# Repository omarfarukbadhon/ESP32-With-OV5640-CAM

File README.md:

## ESP32 With OV5640 CAM 

# 3D of top side PCB 

# 3D of Bottom Side PCB

# Routing of PCB

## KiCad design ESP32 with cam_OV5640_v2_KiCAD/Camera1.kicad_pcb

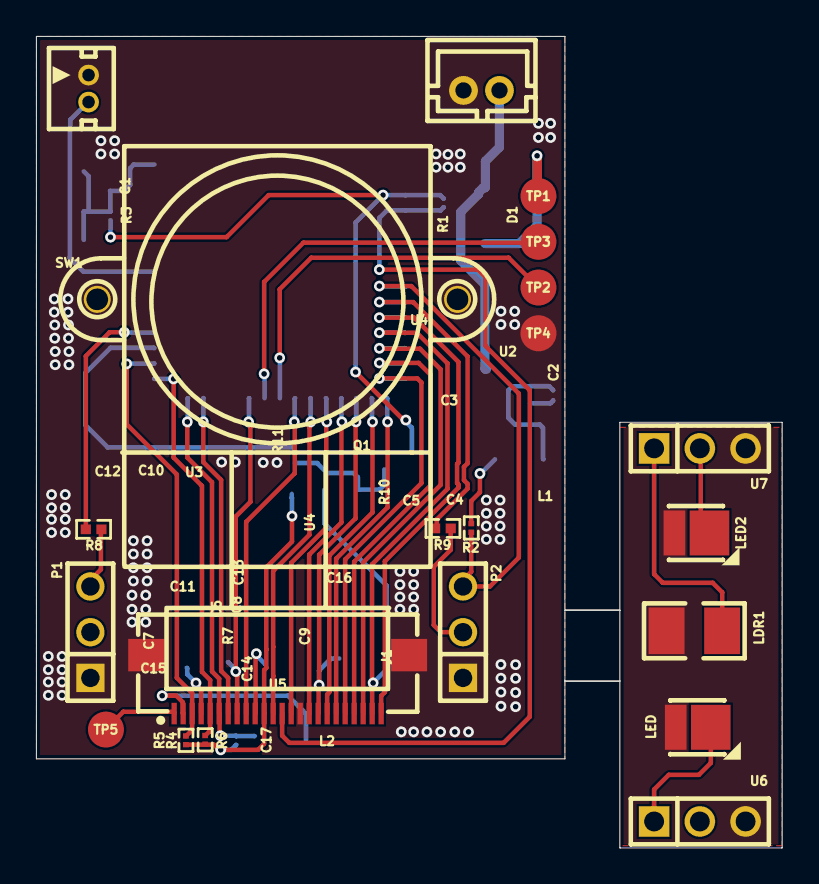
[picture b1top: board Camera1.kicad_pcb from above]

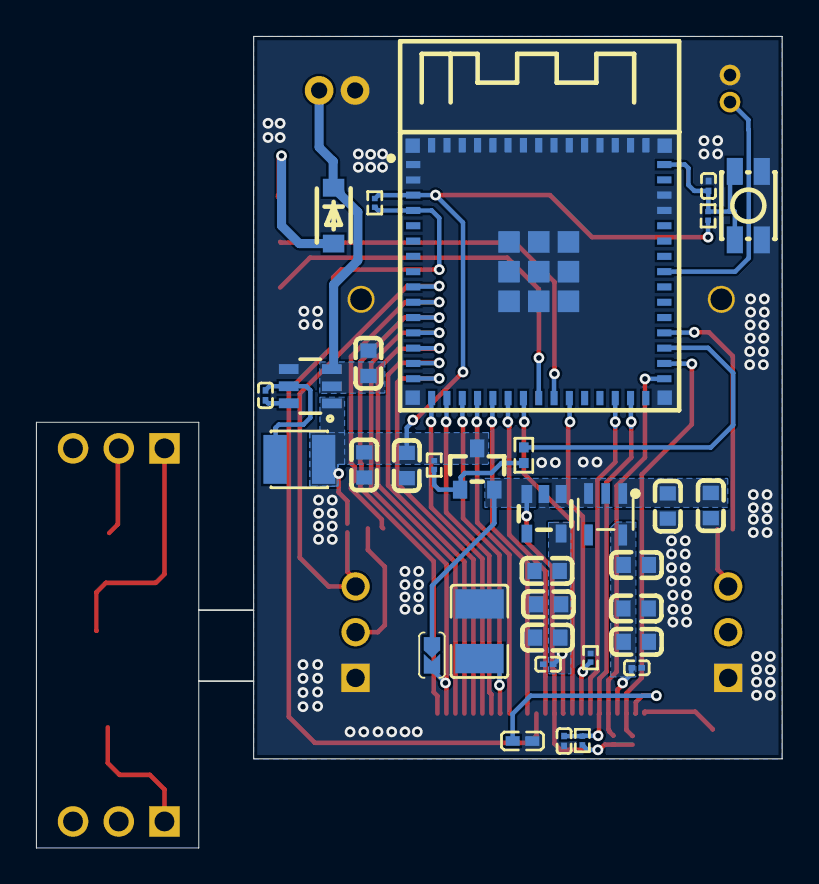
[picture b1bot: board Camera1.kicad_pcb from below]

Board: 2 copper layers, 41.4 x 45.1 mm, 54 parts (33 on the bottom side), 44 nets.

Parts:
C1, C2, C14, C15, C17: 100NF SMD CERAMIC 201
C3, C6, C7, C8, C9: 10UF SMD CERAMIC 603
C4, C5: 22PF SMD CERAMIC 603
C10, C11, C12, C13: 1UF CAP
C16: 22UF SMD CERAMIC 1210
CN1: CONNECTOR 2P
CN2: 2P WHITE CONNECTOR 1.5MM
D1: SCHOTTKY DIODE
J1: PAD-JUMPER-2
L1: 3.9UH POWER INDUCTOR
L2: FERRITE
LDR1: LDR
LED, LED2: LED SMD
P1, P2: 3P FH 2.54MM
Q1: P CHANNEL MSFET (AO3401A1)
R1, R3, R4, R5, R6, R7, R10: 10K SMD CERAMIC 201
R2: 4K7 SMD 201
R8, R9, R11: 100R 402
SW1: PUSH BUTTON 4P
TP1, TP2, TP3, TP4, TP5: TESTPOINT
U1: ESP32-S3-MINI-1-N8
U2: 3V3 CONVERTER (AP63203)
U3: 2V8 CONVERTER (TLV74328)
U4: OV5640
U4#2: 1V5 CONVERTER (TLV74215)
U5: CAMERA CONNECTOR
U6, U7: 3P MH 2.54MM

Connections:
+1V5: C8.2, C9.2, C13.2, C14.2, U4#2.5, U5.10
+2V8: C6.2, C7.2, C11.2, C15.2, U3.5, U5.4
+3V3: C4.2, C5.2, L1.2, Q1.3, R1.2, R2.1, R3.2, R10.1, U1.3, U2.1
+3V3_CAM: C10.2, C12.2, J1.1, Q1.2, R4.2, R5.2, R6.2, U3.1, U3.3, U4#2.1, U4#2.3, U5.11
AGND: L2.2, U5.2
BAT: C3.2, CN1.1, D1.1, U2.2, U2.3
CAM_PWR: R11.1, U1.33
DATA0: U1.11, U5.24
DATA1: J1.2, U1.12, U5.23
DATA2: U1.16, U5.19
DATA3: U1.14, U5.21
DATA4: U1.13, U5.22
DATA5: U1.15, U5.20
DATA6: U1.17, U5.18
DATA7: U1.19, U5.16
DATA8: U1.20, U5.14
DATA9: U1.21, U5.12
GND: C1.1, C3.1, C4.1, C5.1, C6.1, C7.1, C8.1, C9.1, C10.1, C11.1, C12.1, C13.1, C14.1, C15.1, C16.1, C17.1, CN1.2, CN2.1, L2.1, P1.1, P2.1, R7.1, SW1.3, SW1.4, TP4.1, U1.1, U1.2, U1.42, U1.43, U1.46, U1.47, U1.48, U1.49, U1.50, U1.51, U1.52, U1.53, U1.54, U1.55, U1.56, U1.57, U1.58, U1.59, U1.60, U1.GND, U2.4, U3.2, U4#2.2, U5.15, U5.25, U5.26
HSYNC: U1.22, U5.9
IR_CUT: CN2.2, U1.38
LDR: LDR1.2, U7.1
LDR_MCU: P2.3, R2.2, U1.9
LED1: R8.2, U1.34
LED2: R9.2, U1.10
NetC2_1: C2.1, L1.1, U2.5
NetC2_2: C2.2, U2.6
NetQ1_1: Q1.1, R10.2, R11.2
NetTP5_1: TP5.1, U5.1
PCLK: C16.2, U1.18, U5.17
PWDN: R7.2, U1.25, U5.8
RESET: C17.2, R6.1, U1.29, U5.6
RST: C1.2, R3.1, SW1.1, SW1.2, U1.45
SCL: R4.1, U1.31, U5.5
SDA: R5.1, U1.32, U5.3
USB_N: TP2.1, U1.23
USB_P: TP3.1, U1.24
Up1: P1.3, R8.1
Up2: P2.2, R9.1
Up11: LED.2, U6.1
Up22: LED2.2, U7.2
Up_GND: LDR1.1, LED.1, LED2.1, U6.3, U7.3
VSYNC: U1.28, U5.7
XCLK: R1.1, U1.4, U5.13
usb_5V: D1.2, TP1.1

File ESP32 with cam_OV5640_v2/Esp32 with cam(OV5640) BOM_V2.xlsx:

Comment | Description | Designator | Footprint | LibRef | Quantity | Input Voltage | Manufacturer | Manufacturer Part | Maximum Input Voltage | Output Voltage | Supplier Part | Tolerance
TEST POINT |  | +5V, D-, D+, GND, STROBE | TESTPOINT | TEST POINT | 5
100nF | 10V 100nF X5R ±10% 0201 Multilayer Ceramic Capacitors MLCC - SMD/SMT ROHS | C1, C2, C14, C15, C17 | 100nF SMD Ceramic 201 | 100nF SMD Ceramic 201 | 5 |  | muRata(村田) | GRM033R61A104KE84D |  |  | C161466 | ±10%
10uF | 10V 10uF B ±10% 0603 Multilayer Ceramic Capacitors MLCC - SMD/SMT ROHS | C3, C6, C7, C8, C9 | 10uF SMD Ceramic 603 | 10uF SMD Ceramic 603 | 5 |  | muRata(村田) | GRM188B31A106KE69D |  |  | C469532
22pF | 16V 22pF C0G ±5% 0603 Multilayer Ceramic Capacitors MLCC - SMD/SMT ROHS | C4, C5 | 22pF SMD Ceramic 603 | 22pF SMD Ceramic 603 | 2 |  | KEMET(基美) | C0603C220J4GAC7867 |  |  | C561800 | ±5%
1uF | 16V 1uF Y5V -20%~+80% 0603 Multilayer Ceramic Capacitors MLCC - SMD/SMT ROHS | C10, C11, C12, C13 | 1uF Cap | 1uF Ceramic SMD 603 | 4 |  | SAMWHA(三和) | CS1608Y5V105Z160NRB |  |  | C5189821 | -20%~+80%
22uF | 10V 22uF X7R ±10% 1210 Multilayer Ceramic Capacitors MLCC - SMD/SMT ROHS | C16 | 22uF SMD Ceramic 1210 | 22uF SMD Ceramic 1210 | 1 |  | KEMET(基美) | C1210C226K8RACAUTO |  |  | C561843 | ±10%
B2B-PH-K-S(LF)(SN) | 1x2P 2P PH Tin 2 -25℃~+85℃ 2A 1 2mm Brass Direct Insert Plugin,P=2mm Wire To Bo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 | CN1 | Connector 2P | Connector 2P | 1 |  | JST | B2B-PH-K-S(LF)(SN) |  |  | C131337
HDGC1501WV-2P |  | CN2 | 2P white Connector 1.5mm | 2P Connector 1.5mm | 1 |  | HDGC(华德共创) | HDGC1501WV-2P |  |  | C5175212
MBR120VLSFT1G | 20V 300mV@1A 1A SOD-123FL Schottky Diodes ROHS | D1 | Schottky Diode | Schottky Diode | 1 |  | onsemi(安森美) | MBR120VLSFT1G |  |  | C223608
Jumper | SMD JUMPER | J1 | PAD-JUMPER-2 | JUMPER SOLDER BRIDGE | 1
3.9uH | 1.5A 3.9uH ±20% 1.4A SMD,3x3mm Power Inductors ROHS | L1 | 3.9uH power Inductor | 3.9uH SMD PI | 1 |  | cjiang(长江微电) | FNR3015S3R9MT |  |  | C167751 | ±20%
BLM15AG601SN1D | 520mΩ ±25% 600Ω@100MHz 0402 Ferrite Beads ROHS | L2 | Ferrite | BLM15AG601SN1D | 1 |  | muRata(村田) | BLM15AG601SN1D |  |  | C76884 | ±25%
GT36528 | SMD,2.4x3.6mm Photoresistors ROHS | LDR1 | LDR | LDR | 1 |  | JCHL(晶创和立) | GT36528 |  |  | C2904881
XYC-IRC18C-24 |  | LED1, LED2 | LED SMD | LED SMD | 2 |  | NEWOPTO(鑫永诚光电) | XYC-IRC18C-24 |  |  | C2988733
Header-Female-2.54_1x3 |  | P1, P2 | 3P FH 2.54mm | Header-Female-2.54_1x3 | 2 |  | BOOMELE(博穆精密) | 2.54-1*3P母 |  |  | C146243
P_Mos | 30V 4A 44mΩ@10V,4.3A 1.4W 1.3V@250uA 1 Piece P-Channel SOT-23 MOSFETs ROHS | Q1 | P channel msfet (AO3401A1) | P channel msfet (AO3401A1) | 1 |  | AOS | AO3401A |  |  | C15127
10K | 50mW Thick Film Resistors 25V ±1% ±200ppm/℃ 10kΩ 0201 Chip Resistor - Surface M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 | R1, R3, R4, R5, R6, R7, R10 | 10K SMD Ceramic 201 | 10K SMD Ceramic 201 | 7 |  | YAGEO(国巨) | AF0201FR-0710KL |  |  | C143978 | ±1%
100R | 100mW Thick Film Resistors ±100ppm/℃ ±1% 100Ω 0402 Chip Resistor - Surface Moun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 | R8, R9, R11 | 100R 402 | 100R 402 | 3 |  | PANASONIC(松下) | ERJ2RKF1000X |  |  | C413063 | ±1%
TS-1102-5516 | 6mm 5.5mm Round Button 25mA Direct Insert 6mm SPST 100000 Times 1.6N 24V Plugin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 | RST | Push Button 4P | Push Button 4P | 1 |  | SOFNG(硕方) | TS-1102-5516 |  |  | C183624
ESP32-S3-MINI-1-N4R2 |  | U1 | ESP32-S3-MINI-1-N8 | ESP32-S3-MINI-1-N4R2 | 1 |  | ESPRESSIF(乐鑫) | ESP32-S3-MINI-1-N4R2 |  |  | C3013941
AP63203WU-7 | Step-down type Fixed 2A 3.3V 3.8V~32V TSOT-23-6 DC-DC Converters ROHS | U2 | 3V3 Converter (AP63203) | AP63203 | 1 | 3.8V~32V | DIODES(美台) | AP63203WU-7 |  | 3.3V | C780769
TLV74328PDBVR | 300mA 68dB Fixed 2.8V Positive electrode 5.5V SOT-23-5 Voltage Regulators - Lin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 | U3 | 2V8 Converter (TLV74328) | TLV74328 | 1 |  | TI(德州仪器) | TLV74328PDBVR | 5.5V | 2.8V | C408971
TLV74315PDBVR | 300mA Fixed 1.5V Positive electrode 5.5V SOT-23-5 Voltage Regulators - Linear, 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 | U4 | 1V5 Converter (TLV74215) | TLV74315 | 1 |  | TI(德州仪器) | TLV74315PDBVR | 5.5V | 1.5V | C469895
FPC-05FB-24PH20 | Dual-sided contacts / top and bottom connection -25℃~+85℃ Flip type 0.5mm Horiz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 | U5 | Camera Connector | Camera Connector | 1 |  | XUNPU(讯普) | FPC-05FB-24PH20 |  |  | C2856831
HB-PH3-25413PB2GOP |  | U6, U7 | 3P MH 2.54mm | 3P MH 2.54mm | 2 |  | HANBO(汉博) | HB-PH3-25413PB2GOP |  |  | C6332196
 |  |  |  | 4.7K | 1 |  | YAGEO(国巨) | AF0201FR-074K7L |  |  | C2105831 | ±1%

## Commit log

2025-06-15 esp32 with ov5640 cam ptoject
2025-06-15 new design file upload
